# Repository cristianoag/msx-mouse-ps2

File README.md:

# MSX Mouse PS2 Adapter

## Introduction

The MSX Mouse PS2 Adapter is a  device that integrates a PS/2 mouse into an MSX computer, supporting both MSX-mouse and MSX-joystick modes. 
Powered by the Atmel ATTiny2313 microcontroller and clocked at 8 MHz using the built-in oscillator, this adapter brings modern mouse functionality to 
the classic MSX platform.

Based on the work/schema developed by Caro in 2009. http://www.caro.su/msx/mous4msx.htm

## Bill of Materials

The following table lists the components required to build the MSX Mouse PS2 Adapter. The table also includes links to the components on AliExpress. 

|Reference|Value|Description|Qty|Link|
|---|---|---|---|---|
|C1|0.1uF|0805 Ceramic Capacitor|1|[AliExpress](https://s.click.aliexpress.com/e/_DDIDVwZ)|
|C2|10uF|SMD Electrolytic Capacitor|1|[AliExpress](https://s.click.aliexpress.com/e/_Dc9V0lj)|
|R2, R3, R4, R6|0805 Resistor|220R|4|[AliExpress](https://s.click.aliexpress.com/e/_Delg4Xf)|
|R7, R8	|0805 Resistor|4.7K|2|[AliExpress](https://s.click.aliexpress.com/e/_Delg4Xf)|
|R1|0805 Resistor|10K|1|[AliExpress](https://s.click.aliexpress.com/e/_Delg4Xf)|
|R5|0805 Resistor|2K|1|[AliExpress](https://s.click.aliexpress.com/e/_Delg4Xf)|
|D1, D2	|1N4148|SMD Diode|2|[AliExpress](https://s.click.aliexpress.com/e/_Dm2Ty6N)|
|D3|LED|0805 LED|1|[AliExpress](https://s.click.aliexpress.com/e/_DCcqt2p)|
|U1|ATTiny2313-20S|Microcontroller|1|[AliExpress](https://s.click.aliexpress.com/e/_DB4CFg5)|
|JP1, JP2||2.54mm Header|2|[AliExpress](https://s.click.aliexpress.com/e/_DFFPdbL)|
|J1|9-pin D-SUB Female|Joystick Connector|1|[AliExpress](https://s.click.aliexpress.com/e/_DeV4P4z)|
|J2|6-pin Mini-DIN Female|PS/2 Connector|1|[AliExpress](https://s.click.aliexpress.com/e/_DFl1rL3)|

## Firmware and Basic Operation

The current firmware version enables the adapter to function in mouse or joystick emulation mode. Programming the ATTiny2313 is achieved through the MSX by setting the JP1 jumper to the "prog" position (pins 1-2 closed). 
In the "work" position (pins 2-3 closed), the MCU operates in mouse or joystick emulation mode. A JP2 jumper is provided to adjust the mouse resolution, particularly useful when using modern high-resolution optical mice.

To toggle between operation modes, simultaneously press both mouse buttons (left and right). 
The current mode is indicated by an LED: lit for mouse mode, unlit for joystick mode. 
Upon power-up, the default mode is mouse mode (LED is on). A blinking LED with a one-second period signals issues such as an unconnected mouse, a malfunctioning mouse, or a USB<>PS/2 adapter-related problem.

## Programming the ATTiny2313

To program or update the firmware of the Atmel ATTiny2313 microcontroller in the MSX mouse adapter, utilize the prg2313t.com tool. Before running the program, set the JP1 jumper on the controller board to the "prog" position.

The tool, designed for Intel-HEX formatted firmware, sets the FUSES bits for an 8 MHz built-in oscillator.

```bash
prg2313t [file.hex]
```

Ensure that the adapter is connected to a joystick port. In case of an unconnected adapter, an error message is displayed:

```
Error: CHIP is not found on any joystick port: 1 RESET <-: STROBE (Joy-8pin) 17 MOSI <-: TrgA (Joy-6pin) 18 MISO ->: Up (Joy-1pin) 19 SCK <-: TrgB (Joy-7pin) 20 VDD <-: +5V (Joy-5pin) 10 GND : GND (Joy-9pin)
```

For a connected controller, the tool provides information about the connected port, including:

- Signature (branded 3-byte identifier of the MCU)
- Current FUSES values
- Current MK firmware

## License

This work is licensed under a [Creative Commons Attribution-NonCommercial-ShareAlike 4.0 International License](http://creativecommons.org/licenses/by-nc-sa/4.0/).

* If you remix, transform, or build upon the material, you must distribute your contributions under the same license as the original.
* You may not use the material for commercial purposes.
* You must give appropriate credit, provide a link to the license, and indicate if changes were made. You may do so in any reasonable manner, but not in any way that suggests the licensor endorses you or your use.

**ATTENTION**

This project was made for the retro community and not for commercial purposes. So only retro hardware forums and individual people can build this project.

THE SALE OF ANY PART OF THIS PROJECT WITHOUT EXPRESS AUTHORIZATION IS PROHIBITED!

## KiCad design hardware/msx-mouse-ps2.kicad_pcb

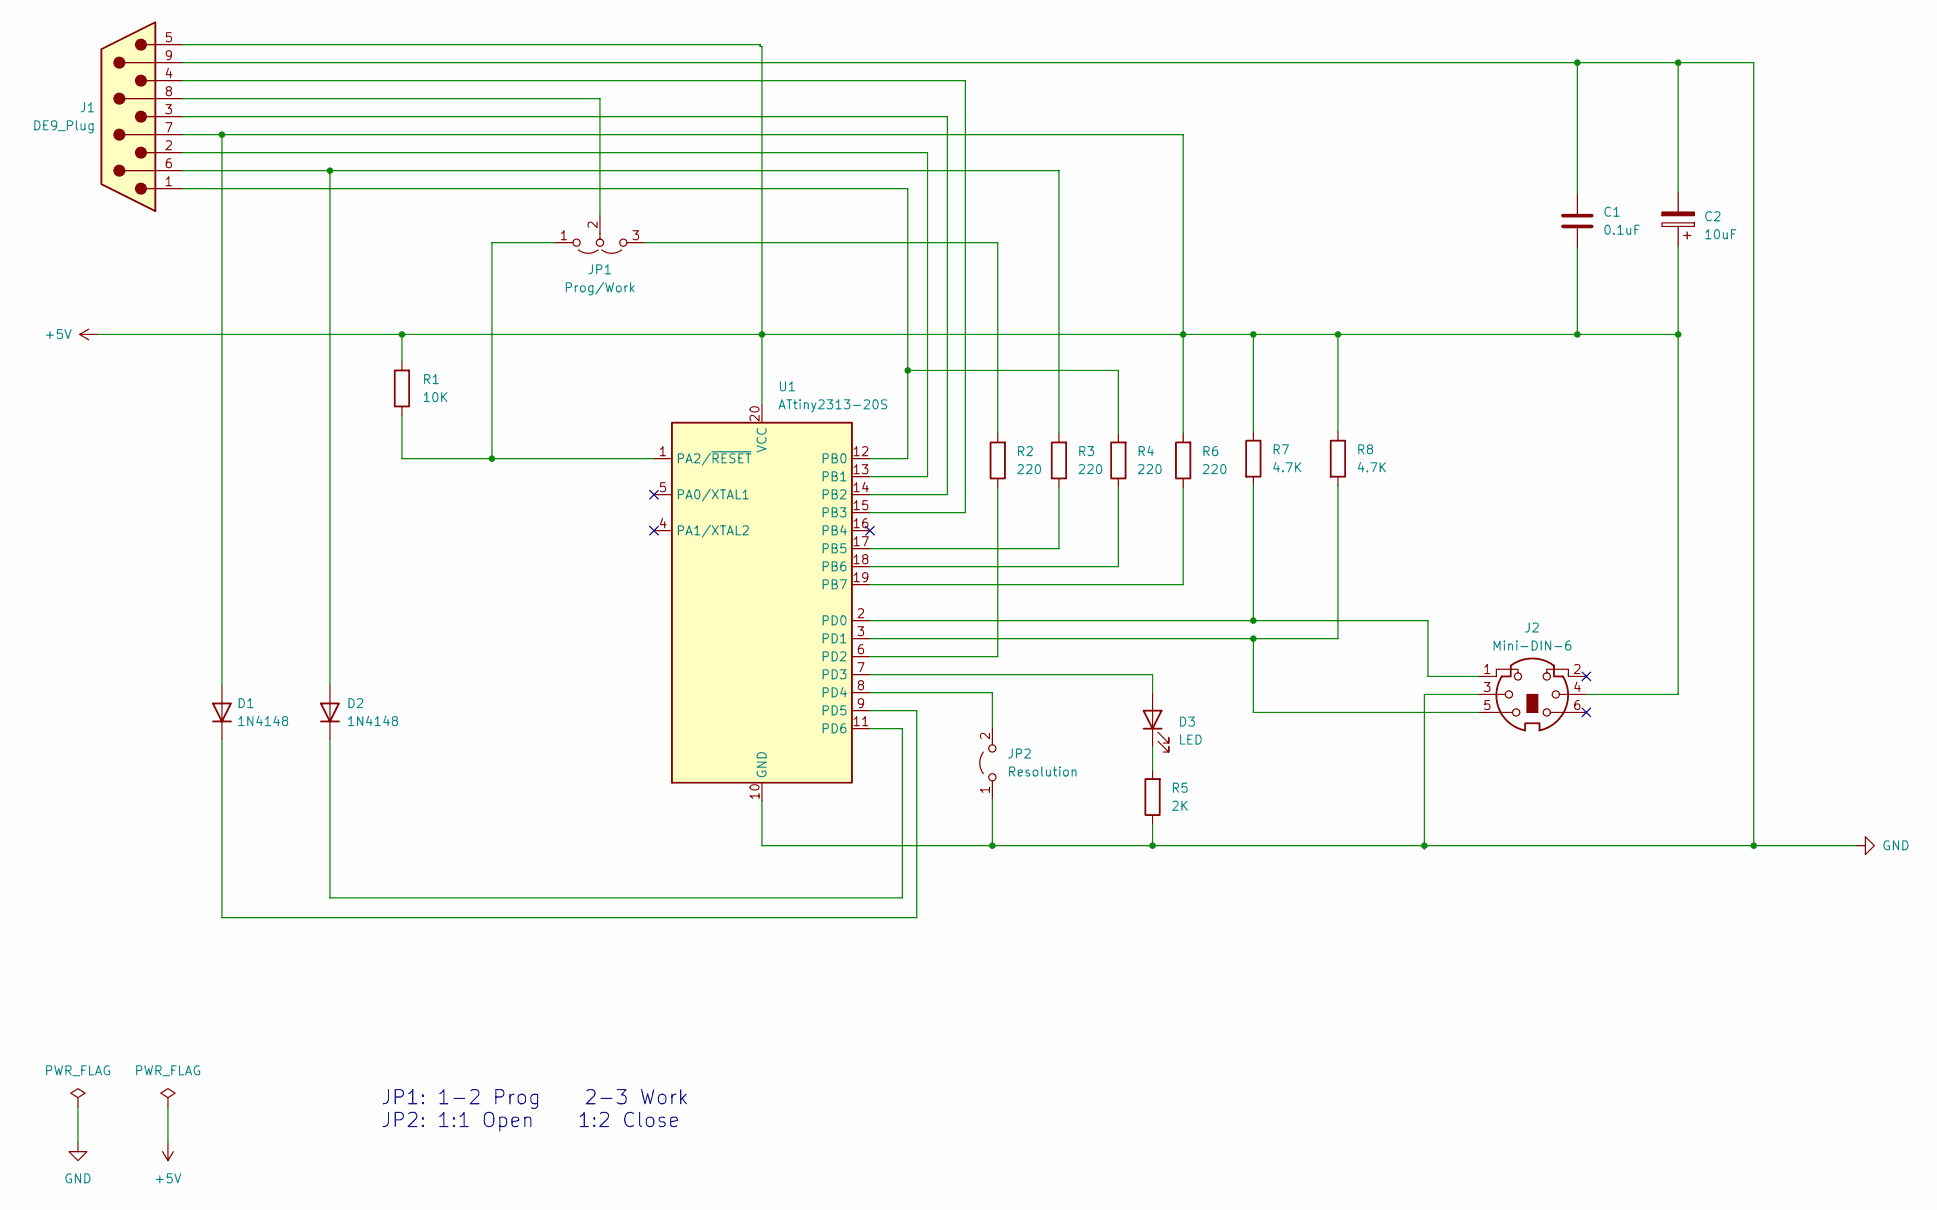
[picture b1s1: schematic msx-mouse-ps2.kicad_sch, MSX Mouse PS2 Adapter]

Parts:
C1: 0.1uF; C_0805_2012Metric_Pad1.18x1.45mm_HandSolder
C2: 10uF; CP_Elec_5x4.5
D1, D2: 1N4148; D_A-405_P10.16mm_Horizontal
D3: LED; LED_0805_2012Metric_Pad1.15x1.40mm_HandSolder
J1: DE9_Plug; DSUB-9_Female_Horizontal_P2.77x2.84mm_EdgePinOffset7.70mm_H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
J2: Mini-DIN-6; TE_5749180-1
JP1: Prog/Work; PinHeader_1x03_P2.54mm_Vertical
JP2: Resolution; PinHeader_1x02_P2.54mm_Vertical
R1: 10K; R_0805_2012Metric_Pad1.20x1.40mm_HandSolder
R2, R3, R4, R6: 220; R_0805_2012Metric_Pad1.20x1.40mm_HandSolder
R5: 2K; R_0805_2012Metric_Pad1.20x1.40mm_HandSolder
R7, R8: 4.7K; R_0805_2012Metric_Pad1.20x1.40mm_HandSolder
U1: ATtiny2313-20S; SOIC-20W_7.5x12.8mm_P1.27mm

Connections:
+5V: C1.2, C2.1, D1.2 (A), J1.5, J1.7, J2.4, R1.2, R6.2, R7.1, R8.1, U1.20 (VCC)
GND: C1.1, C2.2, J1.9, J2.3, JP2.1 (A), R5.1, U1.10 (GND)
unnamed: D1.1 (K), U1.9 (PD5)
unnamed: D2.2 (A), J1.6, R3.2
unnamed: D2.1 (K), U1.11 (PD6)
unnamed: D3.2 (A), U1.7 (PD3)
unnamed: D3.1 (K), R5.2
unnamed: JP1.1 (A), R1.1, U1.1 (PA2/~RESET)
unnamed: JP1.3 (B), R2.2
unnamed: J1.8, JP1.2 (C)
unnamed: JP2.2 (B), U1.8 (PD4)
unnamed: J1.1, R4.2, U1.12 (PB0)
unnamed: J1.2, U1.13 (PB1)
unnamed: J1.3, U1.14 (PB2)
unnamed: J1.4, U1.15 (PB3)
unnamed: R3.1, U1.17 (PB5)
unnamed: R4.1, U1.18 (PB6)
unnamed: R6.1, U1.19 (PB7)
unnamed: J2.1, R7.2, U1.2 (PD0)
unnamed: J2.5, R8.2, U1.3 (PD1)
unnamed: R2.1, U1.6 (PD2)

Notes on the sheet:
JP1: 1-2 Prog 2-3 Work JP2: 1:1 Open 1:2 Close

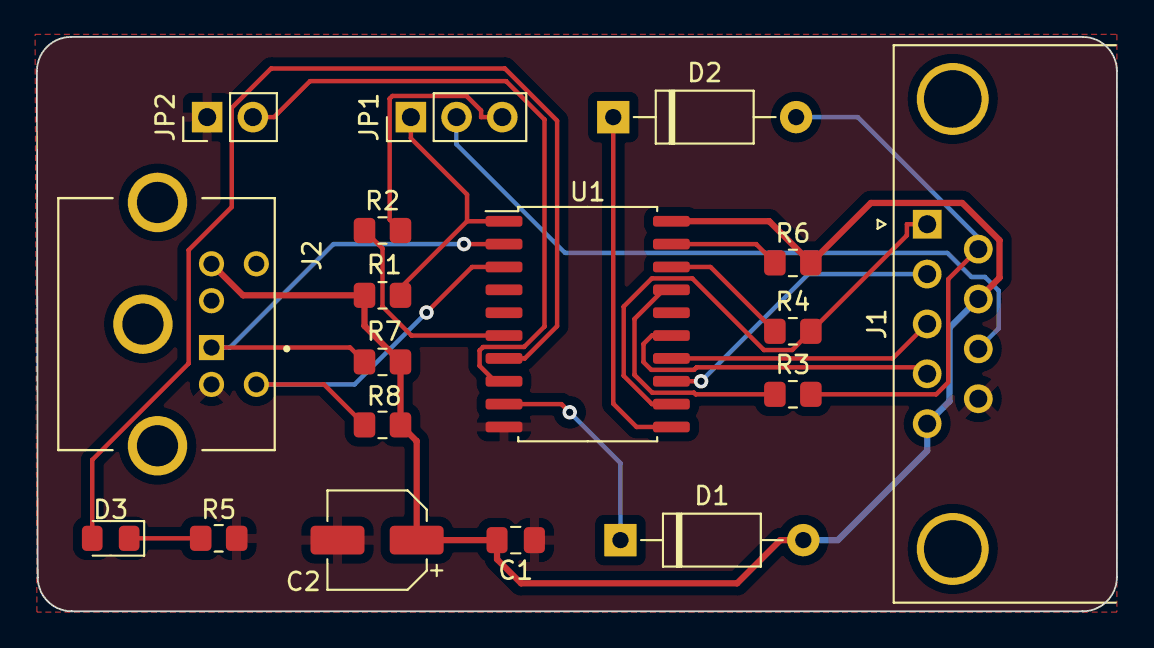
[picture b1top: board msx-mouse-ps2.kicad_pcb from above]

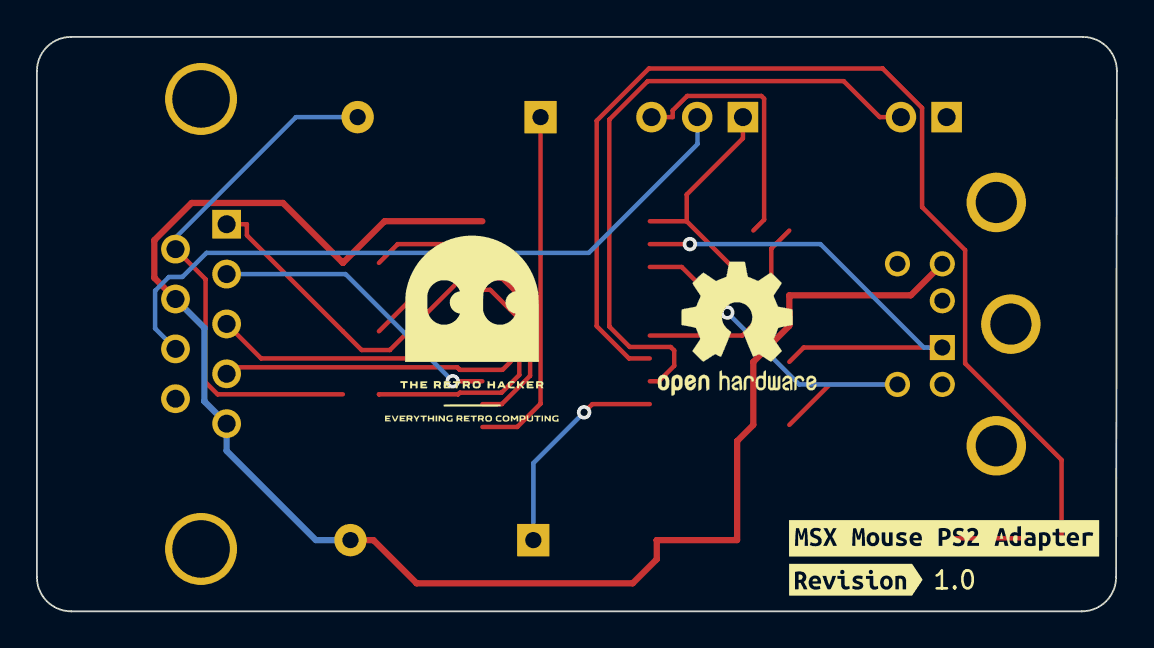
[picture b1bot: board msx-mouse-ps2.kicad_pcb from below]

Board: 2 copper layers, 60.0 x 31.9 mm, 20 parts (2 on the bottom side), 21 nets.

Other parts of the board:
kibuzzard-65A48E6D: G***; kibuzzard-65A48E6D
kibuzzard-65A48E58: G***; kibuzzard-65A48E58

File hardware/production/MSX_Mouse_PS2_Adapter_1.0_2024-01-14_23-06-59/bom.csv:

Designator,Footprint,Quantity,Value,LCSC Part #
C1,0805,1,0.1uF,
C2,CP_Elec_5x4.5,1,10uF,
"D1, D2",D_A-405_P10.16mm_Horizontal,2,1N4148,
D3,0805,1,LED,
J1,DSUB-9_Female_Horizontal_P2.77x2.84mm_EdgePinOffset7.70mm_Housed_MountingHolesOffset9.12mm,1,DE9_Plug,
J2,TE_5749180-1,1,Mini-DIN-6,
JP1,PinHeader_1x03_P2.54mm_Vertical,1,Prog/Work,
JP2,PinHeader_1x02_P2.54mm_Vertical,1,Resolution,
R1,0805,1,10K,
"R2, R3, R4, R6",0805,4,220,
R5,0805,1,2K,
"R7, R8",0805,2,4.7K,
U1,SOIC-20W_7.5x12.8mm_P1.27mm,1,ATtiny2313-20S,

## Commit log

2024-01-15 README
2024-01-15 gerbers and ibom v1
2024-01-15 small fixes
2024-03-10 Minor updates
2024-03-10 Update with the BOM
